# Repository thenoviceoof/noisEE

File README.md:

noiseEE
================================================================================
Code to find a set of easily derivable software filters to produce
different flavors of noise and intermediate stages, and a hardware
realization.

If you want a full explanation of the project, see notes [part
1](http://thenoviceoof.com/blog/projects/noisee-part-1-software/) and
[part
2](http://thenoviceoof.com/blog/projects/noisee-part-2-hardware/).

**NOTE**: the hardware rendition does not work, and will be expensive
in time to correct. This project is abandoned.

filter/
--------------------------------------------------------------------------------
Contains scripts to help find and visualize the filter parameters.

- `exploration_parameters.py`: exploratory work, lots of commented out
  code. Generates graphics to investigate whether simple linear
  parameter interpolation would work.

- `ideal_parameters.py`: hill climb the gain parameters of a joint
  filter made of 3 low pass filters to create linear slope
  approximations, using ideal filter transfer functions. Generates
  `gains.csv`.

- `linear_approximation.R`: takes in `gains.csv` (currently a more
  specific name; you'll need to edit the file) and uses R's segmented
  library to get a piecewise linear approximation. Generates
  `linear_parameters.csv`.

- `generate_hardware_parameter.py`: takes in `linear_parameters.csv`,
  and prints out 16-bit fixed-point integer gain parameters for use in
  `noisEE.c`.

There are also scripts generating multimedia:

- `generate_audio.py`: given the piecemeal results in
  `linear_parameters.csv`, generate a WAV file sweeping from white to
  red noise.

- `visualized_spectrum.py`: running this will generate figures used in
  [part 1 of the project
  notes](http://thenoviceoof.com/blog/projects/noisee-part-1-software/).

- `visualized_animated_spectrum.py`: running this will generate
  animation frames used for the spectrum animation in [part 1 of the
  project
  notes](http://thenoviceoof.com/blog/projects/noisee-part-1-software/).

hardware/
--------------------------------------------------------------------------------
Contains the hardware design files.

- `noisEE-project*`: KiCad design files. Start with the `.pro` project file.

- `noisEE-components*`: contains the OPA227 symbol and MEE1SC footprint
  for KiCad.

- `case__1_5mm.svg/case__3_0mm.svg`: the SVG design files fit into
  Ponoko's P1 template, meant for their respective wood thicknesses.

- `case_*.svg`: these SVGs are intermediate design files, mostly
  correcting for laser kerf.

avr/
--------------------------------------------------------------------------------
Contains files for programming the AVR.

- `Makefile`: just run `make` to build and upload, if you have `avr-gcc`
  and `avrdude` on your path, and are using the ISP MKII. You'll need
  to edit this file if you're using something else.

- `noisEE.c`: currently in a bad state, checkpointed in the middle of
  testing how each filter affects the final response. If you want to
  continue work, you'll need to remove the test loop and uncomment the
  real runtime loop.

(other)
--------------------------------------------------------------------------------

- `test_binary_search_loop.py`: a quick script to make sure that a
  binary search on the calculated filter values will terminate.

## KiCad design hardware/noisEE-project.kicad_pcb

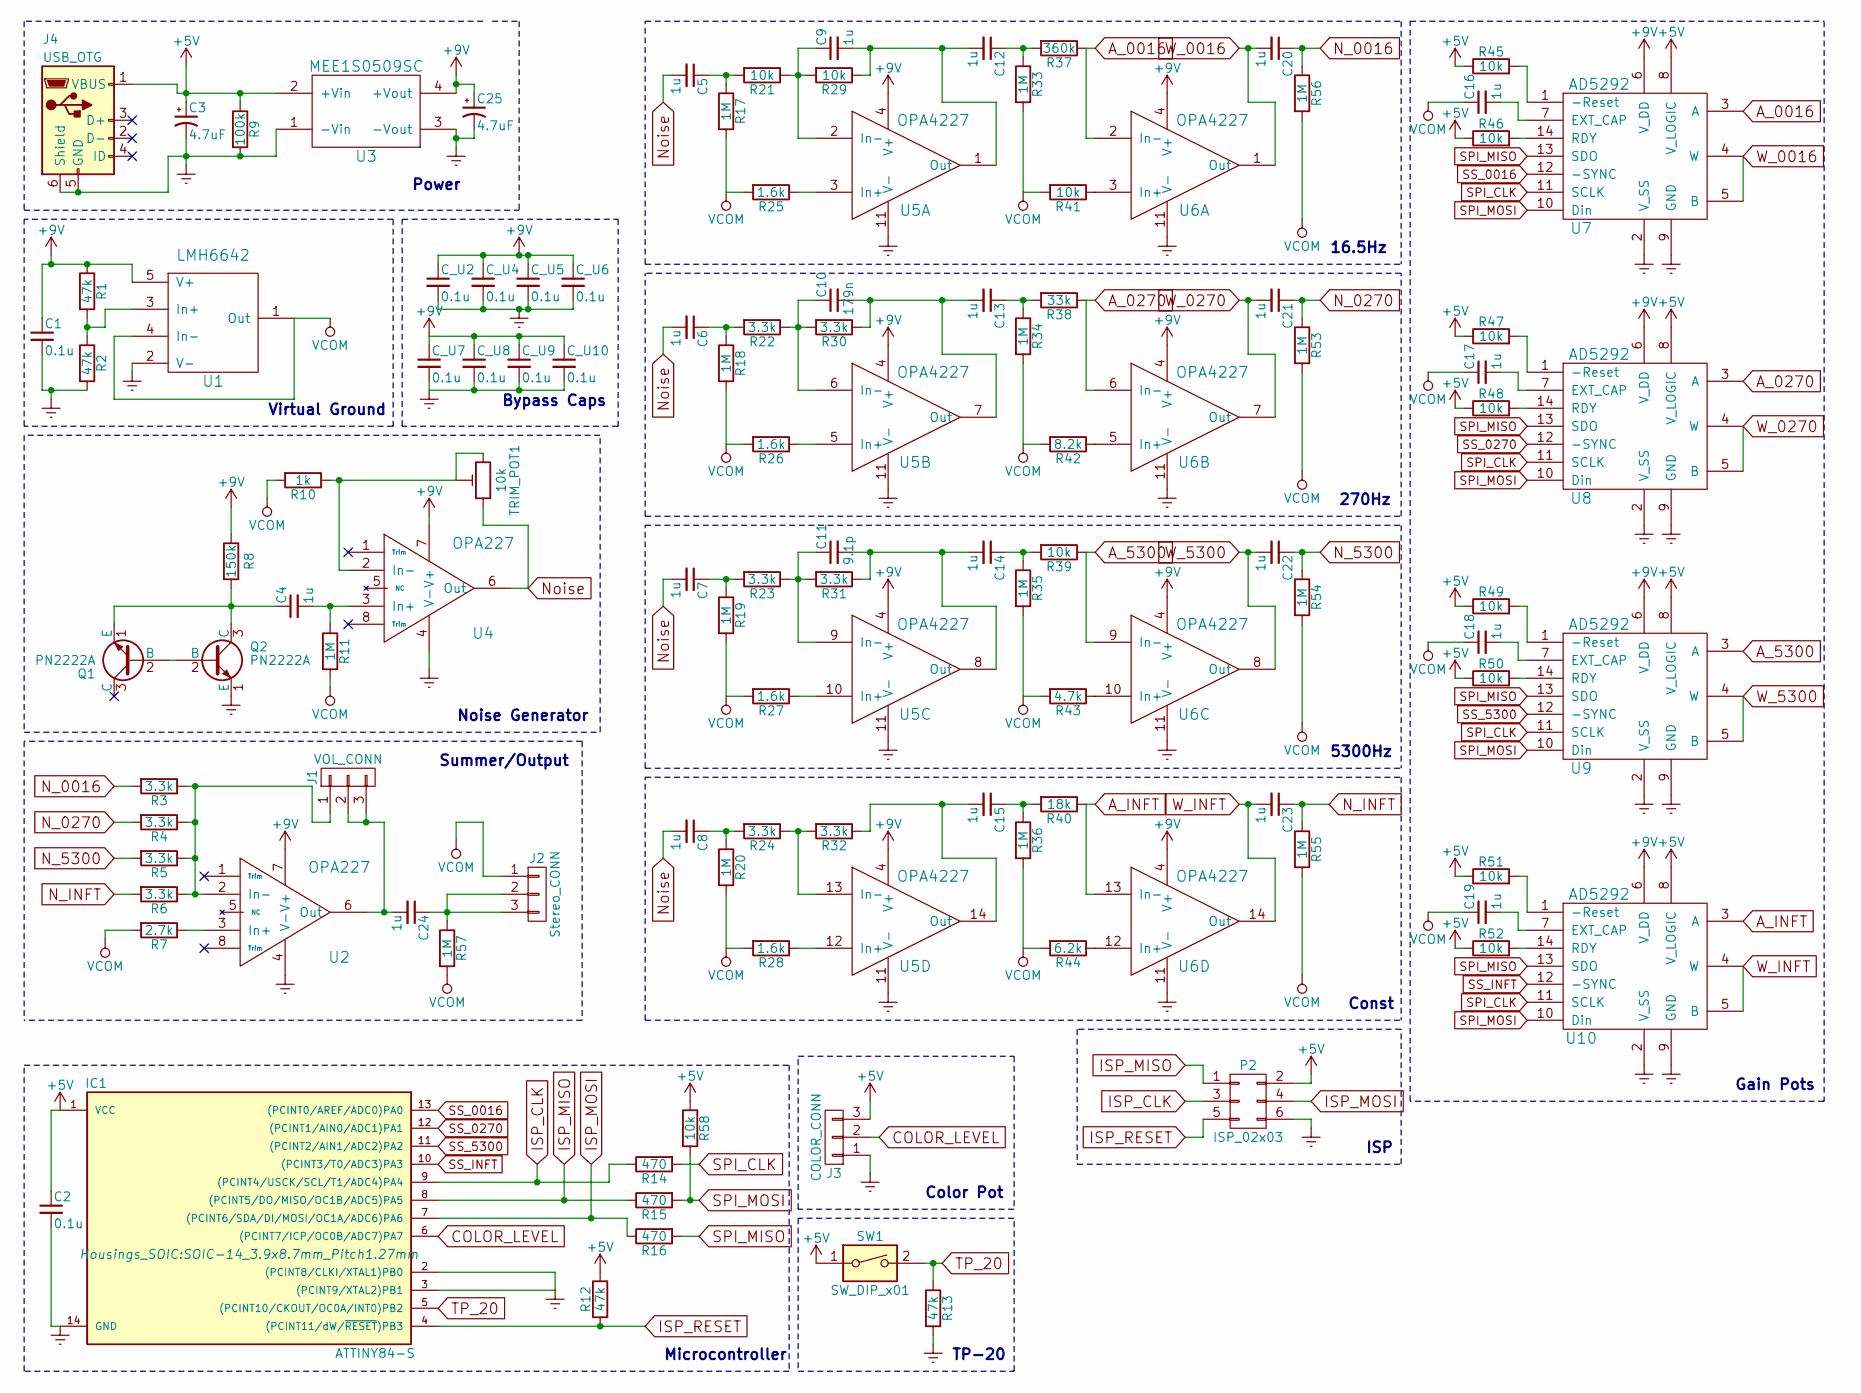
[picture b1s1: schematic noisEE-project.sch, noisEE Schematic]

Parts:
C1, C2: 0.1u; C_0805
C3, C25: 4.7uF; CP_Radial_D8.0mm_P3.50mm
C4, C5, C6, C7, C8, C9, C12, C13, C14, C15, C16, C17, C18, C19, C20, C21, C22, C23, C24: 1u; C_0805
C10: 179n; C_0805
C11: 9.1p; C_0805
C_U2, C_U4, C_U5, C_U6, C_U7, C_U8, C_U9, C_U10: 0.1u; C_0805
IC1: ATTINY84-S; SOIC-14_3.9x8.7mm_Pitch1.27mm
J1: VOL_CONN; Pin_Header_Straight_1x03_Pitch2.54mm
J2: Stereo_CONN; Pin_Header_Straight_1x03_Pitch2.54mm
J3: COLOR_CONN; Pin_Header_Straight_1x03_Pitch2.54mm
J4: USB_OTG; USB_Micro-B_10103594-0001LF
P2: ISP_02x03; Pin_Header_Straight_2x03_Pitch2.54mm
Q1, Q2: PN2222A; TO-92_Inline_Wide
R1, R2, R12, R13: 47k; R_0805
R3, R4, R5, R6, R22, R23, R24, R30, R31, R32: 3.3k; R_0805
R7: 2.7k; R_0805
R8: 150k; R_0805
R9: 100k; R_0805
R10: 1k; R_0805
R11, R17, R18, R19, R20, R33, R34, R35, R36, R53, R54, R55, R56, R57: 1M; R_0805
R14, R15, R16: 470; R_0805
R21, R29, R39, R41, R45, R46, R47, R48, R49, R50, R51, R52, R58: 10k; R_0805
R25, R26, R27, R28: 1.6k; R_0805
R37: 360k; R_0805
R38: 33k; R_0805
R40: 18k; R_0805
R42: 8.2k; R_0805
R43: 4.7k; R_0805
R44: 6.2k; R_0805
SW1: SW_DIP_x01; SW_TH_Tactile_Omron_B3F-10xx
TRIM_POT1: 10k; Potentiometer_Trimmer_Bourns_3339P_Horizontal
U1: LMH6642; SOT-23-5
U2, U4: OPA227; SOIC-8_3.9x4.9mm_Pitch1.27mm
U3: MEE1S0509SC; MEE1SC
U5, U6: OPA4227; SOIC-14_3.9x8.7mm_Pitch1.27mm
U7, U8, U9, U10: AD5292; TSSOP-14_4.4x5mm_Pitch0.65mm

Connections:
+5V: C2.1, C3.1, IC1.1 (VCC), J3.3, J4.1 (VBUS), P2.2, R9.1, R12.1, R45.1, R46.1, R47.1, R48.1, R49.1, R50.1, R51.1, R52.1, R58.1, SW1.1, U3.2 (+Vin), U7.8 (V_LOGIC), U8.8 (V_LOGIC), U9.8 (V_LOGIC), U10.8 (V_LOGIC)
+9V: C1.1, C25.1, C_U2.1, C_U4.1, C_U5.1, C_U6.1, C_U7.1, C_U8.1, C_U9.1, C_U10.1, R1.1, R8.1, U1.5 (V+), U2.7 (V+), U3.4 (+Vout), U4.7 (V+), U5.4 (V+), U6.4 (V+), U7.6 (V_DD), U8.6 (V_DD), U9.6 (V_DD), U10.6 (V_DD); also elsewhere on the board
A_0016: R37.1, U6.2 (In-), U7.3 (A)
A_0270: R38.1, U6.6 (In-), U8.3 (A)
A_5300: R39.1, U6.9 (In-), U9.3 (A)
A_INFT: R40.1, U6.13 (In-), U10.3 (A)
COLOR_LEVEL: IC1.6 ((PCINT7/ICP/OC0B/ADC7)PA7), J3.2
Earth: C1.2, C2.2, C3.2, C25.2, C_U2.2, C_U4.2, C_U5.2, C_U6.2, C_U7.2, C_U8.2, C_U9.2, C_U10.2, IC1.2 ((PCINT8/CLKI/XTAL1)PB0), IC1.3 ((PCINT9/XTAL2)PB1), IC1.14 (GND), J3.1, J4.5 (GND), J4.6 (Shield), P2.6, Q2.1 (E), R2.2, R9.2, R13.2, U1.2 (V-), U2.4 (V-), U3.1 (-Vin), U3.3 (-Vout), U4.4 (V-), U5.11 (V-), U6.11 (V-), U7.2 (V_SS), U7.9 (GND), U8.2 (V_SS), U8.9 (GND), U9.2 (V_SS), U9.9 (GND), U10.2 (V_SS), U10.9 (GND); also elsewhere on the board
ISP_CLK: IC1.9 ((PCINT4/USCK/SCL/T1/ADC4)PA4), P2.3, R14.1
ISP_MISO: IC1.8 ((PCINT5/DO/MISO/OC1B/ADC5)PA5), P2.1, R15.1
ISP_MOSI: IC1.7 ((PCINT6/SDA/DI/MOSI/OC1A/ADC6)PA6), P2.4, R16.1
ISP_RESET: IC1.4 ((PCINT11/dW/~RESET~)PB3), P2.5, R12.2
N_0016: C20.1, R3.2, R56.1
N_0270: C21.1, R4.2, R53.1
N_5300: C22.1, R5.2, R54.1
N_INFT: C23.1, R6.2, R55.1
unnamed: C4.1, Q1.1 (E), Q2.3 (C), R8.2
unnamed: C4.2, R11.1, U4.3 (In+)
unnamed: C5.1, R17.1, R21.2
unnamed: C6.1, R18.1, R22.2
unnamed: C7.1, R19.1, R23.2
unnamed: C8.1, R20.1, R24.2
unnamed: C9.1, R21.1, R29.2, U5.2 (In-)
unnamed: C10.1, R22.1, R30.2, U5.6 (In-)
unnamed: C10.2, C13.2, R30.1, U5.7 (Out)
unnamed: C11.1, R23.1, R31.2, U5.9 (In-)
unnamed: C11.2, C14.2, R31.1, U5.8 (Out)
unnamed: C12.1, R33.1, R37.2
unnamed: C9.2, C12.2, R29.1, U5.1 (Out)
unnamed: C13.1, R34.1, R38.2
unnamed: C14.1, R35.1, R39.2
unnamed: C15.1, R36.1, R40.2
unnamed: C15.2, R32.1, U5.14 (Out)
unnamed: C16.2, U7.7 (EXT_CAP)
unnamed: C17.2, U8.7 (EXT_CAP)
unnamed: C18.2, U9.7 (EXT_CAP)
unnamed: C19.2, U10.7 (EXT_CAP)
unnamed: C24.1, J2.2, J2.3, R57.1
unnamed: C24.2, J1.2, J1.3, U2.6 (Out)
unnamed: J1.1, R3.1, R4.1, R5.1, R6.1, U2.2 (In-)
unnamed: Q1.2 (B), Q2.2 (B)
unnamed: R1.2, R2.1, U1.3 (In+)
unnamed: R7.1, U2.3 (In+)
unnamed: R10.1, TRIM_POT1.2, TRIM_POT1.3, U4.2 (In-)
unnamed: R24.1, R32.2, U5.13 (In-)
unnamed: R25.1, U5.3 (In+)
unnamed: R26.1, U5.5 (In+)
unnamed: R27.1, U5.10 (In+)
unnamed: R28.1, U5.12 (In+)
unnamed: R41.1, U6.3 (In+)
unnamed: R42.1, U6.5 (In+)
unnamed: R43.1, U6.10 (In+)
unnamed: R44.1, U6.12 (In+)
unnamed: R45.2, U7.1 (-Reset)
unnamed: R46.2, U7.14 (RDY)
unnamed: R47.2, U8.1 (-Reset)
unnamed: R48.2, U8.14 (RDY)
unnamed: R49.2, U9.1 (-Reset)
unnamed: R50.2, U9.14 (RDY)
unnamed: R51.2, U10.1 (-Reset)
unnamed: R52.2, U10.14 (RDY)
Noise: C5.2, C6.2, C7.2, C8.2, TRIM_POT1.1, U4.6 (Out)
SPI_CLK: R14.2, U7.11 (SCLK), U8.11 (SCLK), U9.11 (SCLK), U10.11 (SCLK)
SPI_MISO: R16.2, U7.13 (SDO), U8.13 (SDO), U9.13 (SDO), U10.13 (SDO)
SPI_MOSI: R15.2, R58.2, U7.10 (Din), U8.10 (Din), U9.10 (Din), U10.10 (Din)
SS_0016: IC1.13 ((PCINT0/AREF/ADC0)PA0), U7.12 (-SYNC)
SS_0270: IC1.12 ((PCINT1/AIN0/ADC1)PA1), U8.12 (-SYNC)
SS_5300: IC1.11 ((PCINT2/AIN1/ADC2)PA2), U9.12 (-SYNC)
SS_INFT: IC1.10 ((PCINT3/T0/ADC3)PA3), U10.12 (-SYNC)
TP_20: IC1.5 ((PCINT10/CKOUT/OC0A/INT0)PB2), R13.1, SW1.2
VCOM: C16.1, C17.1, C18.1, C19.1, J2.1, R7.2, R10.2, R11.2, R17.2, R18.2, R19.2, R20.2, R25.2, R26.2, R27.2, R28.2, R33.2, R34.2, R35.2, R36.2, R41.2, R42.2, R43.2, R44.2, R53.2, R54.2, R55.2, R56.2, R57.2, U1.1 (Out), U1.4 (In-)
W_0016: C20.2, U6.1 (Out), U7.4 (W), U7.5 (B)
W_0270: C21.2, U6.7 (Out), U8.4 (W), U8.5 (B)
W_5300: C22.2, U6.8 (Out), U9.4 (W), U9.5 (B)
W_INFT: C23.2, U6.14 (Out), U10.4 (W), U10.5 (B)

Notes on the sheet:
Power
Noise Generator
Summer/Output
Virtual Ground
16.5Hz
270Hz
5300Hz
Const
ISP
TP-20
Color Pot
Microcontroller
Gain Pots
Bypass Caps

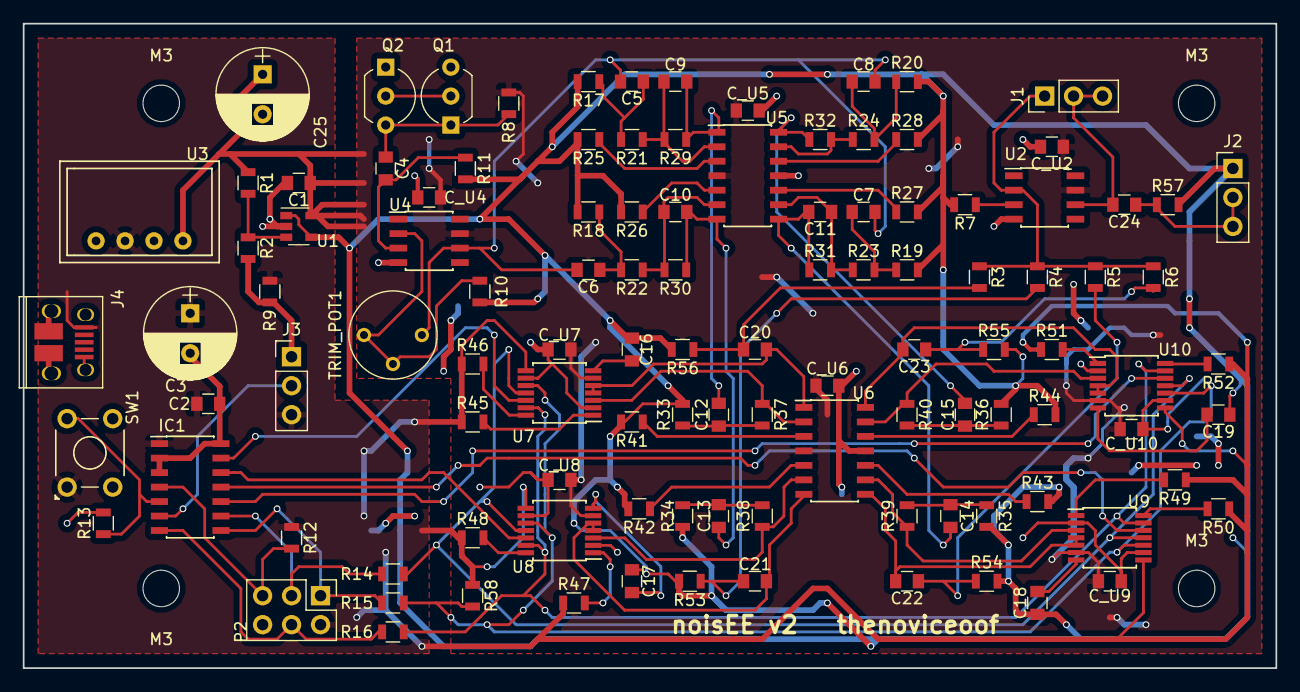
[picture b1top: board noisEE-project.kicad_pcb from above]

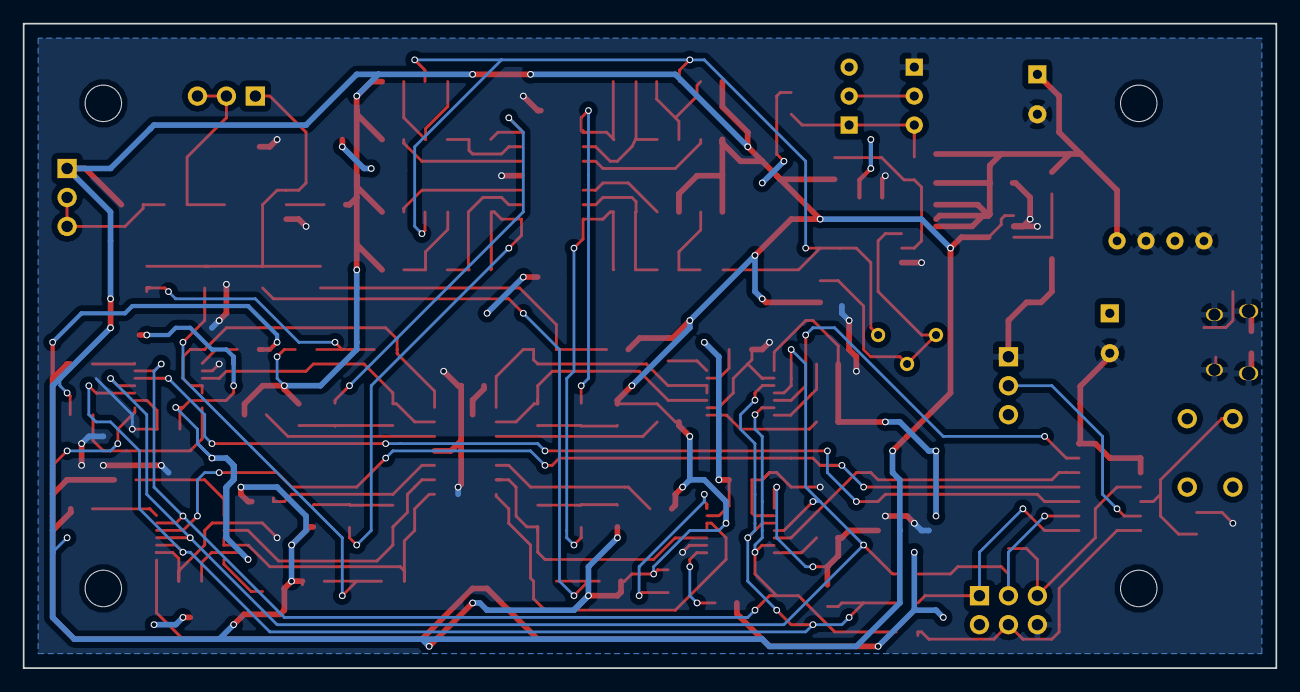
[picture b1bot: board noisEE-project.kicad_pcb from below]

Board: 2 copper layers, 109.9 x 56.5 mm, 123 parts (2 on the bottom side), 75 nets.

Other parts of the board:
A: plane_pad
B: plane_pad
C: plane_pad
D: plane_pad
M3, M3#2, M3#3, M3#4: MountingHole_3.2mm_M3
X: plane_pad
Y: plane_pad
Z: plane_pad
e: plane_pad

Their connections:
+9V: D.1, X.1, e.1; also elsewhere on the board
Earth: A.1, B.1, C.1, Y.1, Z.1; also elsewhere on the board

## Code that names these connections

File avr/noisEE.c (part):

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        // Set up the SPI communications channels.
        DDRA |=
                // Set the direction for the chip select pins
                // (PA0/PA1/PA2/PA3 for 16,270,5300,inft
                // respectively).
                (1 << PCINT0) | (1 << PCINT1) | (1 << PCINT2) | (1 << PCINT3)
                // Set the direction for the SPI pins SCL and MOSI
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
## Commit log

2015-01-02 Restarting with just the README
2015-01-02 Ignore testing WAVs
2015-01-02 Start with a skeleton script
2015-01-02 Fetch the wav data
2015-01-02 Get the fft data
2015-01-02 Use a SAMPLE_RATE constant instead of a bare 44.1k
2015-01-04 Normalize the fft data, convert to decibels correctly
2015-01-04 Add a cli switch for changing the FFT bucket size
2015-01-04 Average multiple buckets of samples for better spectral accuracy
2015-01-04 Get the slope/error from the lg-lg plot
2015-01-05 Return something closer to expected error (?)
2015-01-05 Add a display option for checking spectra graphically with matplotlib
2015-01-05 Add a more user-friendly way to display errors
2015-01-05 Add sections
2015-01-05 Remove restriction on size of audio
2015-01-05 Check if the FFT size is a power of 2
2015-01-07 Add plots to visualization
2015-01-07 Add a way to apply filters
2015-01-07 Move the slope/filter application into a function
2015-01-07 Add target slope for pinking filter
2015-01-12 Add a possibly broken hill climbing algorithm
2015-01-12 Use the error combination algo as the input to the jitter algo
2015-01-12 REBASE ME into the hill climbing algo
2015-01-12 Tweak the jitter function to not immediately crash
2015-01-12 Add some verbose switch debug print statements
2015-01-12 Use the hill-climber in main
2015-01-14 Try to avoid problems with numpy with deepcopy
2015-01-14 Update verbose print statements
2015-01-14 Catch floating point overflow errors (caused by bad filters)
2015-01-14 Possibly better error combination fn
2015-01-14 Modify the new combined error function
2015-01-14 Print calculated combined error in verbose statements
2015-01-15 ML algo fixes (bad max, error fn too discontinuous, weight up error
2015-01-15 Use a multiprocessing approach for parallelism
2015-01-15 Clear the updating jitter lines before printing to them
2015-01-16 Add a iteration cap, to prevent run aways
2015-01-16 Remove code related to display spectra
2015-01-16 Pass all the arguments possible through main
2015-01-16 Pass args through to main, add CLI arguments
2015-01-16 Fix the worker shutdown routines
2015-01-16 Pass verbose through, instead of treating as stuck switch
2015-01-16 Add a simple filter definitions for white noise
2015-01-16 Add the ability to iterate over multiple slopes
2015-01-18 Add levels of verbosity (clean up the jitter replacement output when piping to file)
2015-01-19 Make the script executable
2015-01-19 Force debug output to print, if stdout is being redirected
2015-01-19 Implement a pressure system to get out of local minima
2015-01-19 Fix the verbose print checks
2015-01-19 Introduce a spin cap, to prevent the algorithm from trying too much while spinning
2015-01-20 Add a --filter-size cli arg to allow changing the number of filters
2015-01-20 Use local max pressure as a forcer for multiple parameter changes
2015-01-22 Move things out of the script and into a lib (prep for 2nd script)
2015-02-02 Fix bug in the lib
2015-02-02 Add a fn for getting lg spectrum data to play with
2015-02-02 Play with figuring out how to derive the knee from the filter params
2015-02-02 Clean up a bit
2015-02-04 Average over spectra, and then apply the polyfit
2015-02-04 Pass in degree as a variable
2015-02-08 Add a script to explore the passband behavior of various filter params
2015-02-08 Be clearer
2015-02-08 More (flipping axis/printing) flags for everyone!
2015-02-08 subplot that shit! polyfit all the times!
2015-02-11 Add a little utility to smooth out the frequency graphs, to get better/less noisy spectrums
2015-02-11 Apply the smoothing utility to the knee spectra
2015-02-11 Do several polyfits to see dependence on degree
2015-02-16 Get log slope from data + switch
2015-02-16 Remove polyfit on X/Z, plot the polys for Y/Z
2015-02-16 Output the X level being fit at
2015-02-16 Smooth the spectrum before doing fits and maxes on it
2015-02-16 Gather characteristics results work into one place
2015-02-18 Run into some problems with negative knees, re-do the knee calculator, optimizing for fit determination
2015-02-18 Make some changes based on bugs found while poking around
2015-02-18 add tool to see what filters do what (idealized)
2015-03-05 Try to truncate the data going into the fitter, compare images
2015-03-12 Try to model the knee frequency as an inverse + linear component
2015-03-12 Create a script to compare actual/ideal filters, explore smoothing behavior
2015-03-15 Add a simple loess smoother (works better than weighted smooth
2015-04-05 Add NCT processing
2015-04-05 Add multiprocessing to knee calcs, tweak
2015-04-05 Update knee calculation
2015-04-05 Tweaks to filter_compare display/ideal filter fn
2015-04-05 Add a fixed-point digital filter applier
2015-04-05 Add digital filter to the filter comparisons
2015-04-12 Get input/output bit filters (and internal state filters) actually working
2015-04-13 New script to search for knee/pass parameters (not white/state) to get slopes
2015-04-14 Get better error combination, do the random walk
2015-04-14 Add better reporting
2015-04-15 Doc tweaks
2015-04-15 Add nct-like caching (no incremental caching built-in)
2015-04-15 Separate reporting/admin from the actual optimization process
2015-04-15 Add pressure mechanism for loop termination/jitter width
2015-04-29 Add multiprocessing support for analog filter search
2015-04-29 Fix bug in analog filter search, loading previous data
2015-04-29 Use gaussian noise instead of uniform noise
2015-04-29 Fix pressure mechanism (accidentally inverted), up pressure amount
2015-04-29 Use a faster growing pressure mechanism (used to top out at 1db variance)
2015-04-29 Fix (?) origin error calculation
2015-05-01 Change all the parameters at once, to overcome single parameter traps
2015-05-01 Allow quitting out of the multiprocessing pool
2015-05-01 How the fuck was this working before? Completely mangled the input structure
2015-05-08 Tinker with the error function
2015-05-08 Ignore sources of error / explain how we're ignoring
2015-05-08 Add random preseed evaluation: really make sure we aren't getting stuck in a local minima
2015-05-08 tinker with the random stepping function step size
2015-05-11 Handle failing workers (passing None)
2015-05-11 Use a looser definition of pressure
2015-05-11 Lower the origin error again
2015-05-11 Since we're using a looser definition of pressure, use that for exit conditions
2015-05-11 Ignore logs and temp files
2015-05-11 Restrict random preseeding to a smaller range
2015-05-12 Allow tweaking parameters from the CLI (+ simplify pressure iterations)
2015-05-13 Fix things up after looking at actual output
2017-01-02 Move the code that I don't know any more to an archive directory
2017-01-02 Explore a bit with ideal parameters
2017-01-02 Generate parameters to match the slope/intercept
2017-01-02 Ignore csv data files
2017-01-03 Check how many times the optimization algorithm actually changes its mind
2017-01-03 Get smoother results (even smoother
2017-01-03 Use the segmented library to find a piecemeal linear approximation for each gain curve
2017-01-04 Oops, the commas are tripping up the comma part of CSV
2017-01-04 Get some audio generation going, to verify that the linear interpolation works
2017-01-04 Try to boost up the middle of the gain functionality
2017-01-07 Make the chunk count a parameter
2017-01-07 Fix incorrect column names in linear_parameters.csv
2017-01-07 Add discrete steps to the gain setting
2017-03-11 Hardware checkpoint: schematic done, PCB fits, traces need layout
2017-03-11 Use two opamps for pre-amp and output stages, clean up board and lay down tracks for all signal paths
2017-03-11 Laid down almost all tracks. GND and Earth seem to be treated as synonyms
2017-03-12 Split up the ground (GND->VCOM)
2017-03-12 Get the plane stiches to stay in with hacky net bindings
2017-03-12 Various tweaks: expanding some pours, moved the USB side mounting holes
2017-03-13 Finish a piled-on design for the case
2017-03-13 Try and compensate for kerf in cut designations
2017-03-13 Separate 3mm and 1.5mm board cuts
2017-03-13 Clean up the cuts, lay out all the cuts separately
2017-03-15 Correct for 3.2mm thick sides, not 3mm
2017-03-15 Import current designs into inkscape templates
2017-05-25 Add compiling AVR code
2017-05-25 Generate 15 bit hardware interpolation parameters.
2017-05-26 Ignore AVR generated files
2017-05-27 Add a makefile for the chip code
2017-05-27 Whoops, change the function name to match
2017-05-27 Update gitignore to ignore the hex files, too
2017-08-20 Check in v2 hardware with fixes for USI and AD5292 Vss issues
2017-08-20 Isolate the top plate changes for v2 (mostly wider)
2017-08-20 Remove bak files, and filter them out with .gitignore
2017-08-20 Put 'art' into another directory
2017-08-24 Make sure that the binary search over the eco-params will always exit
2017-08-27 Check in the current AVR code, warts and testing code and all
2017-08-27 Checkin seemingly marginal svg diffs, probably version differences
2017-09-01 Switch the generate_audio script to doing a per-sample filter change
2017-09-04 Add extra descriptiveness to the linear approximation plots, like titles/axis labels
2017-09-07 Generate some example spectra for the blog post
2017-10-07 Generate a series of spectral filter outputs for an animation
2017-10-07 Update KiCad project files for library rescue
2017-10-07 Move filter python scripts into a filter/ directory
2017-10-07 Remove the archive/ directory
2017-10-07 Update the README with explanations of each file, and links back to the project notes
2017-10-07 Whoopsie: fix broken project note links
2017-10-07 Update the README to make it clear that the project is abandoned
2017-10-07 Apply the Apache 2 license
2017-12-03 Fix up the README.md with some unclear sections and missing markup.

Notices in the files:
avr/noisEE.c:
Copyright 2017 "Nathan Hwang" <thenoviceoof>
Licensed under the Apache License, Version 2.0 (the "License");
